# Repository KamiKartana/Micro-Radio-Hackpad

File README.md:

# Hackpad-Mini-Radio-Shaped-Keyboard
A small keyboard to help control settings for a music player easily. While still looking and functioning like an old timey radio. Made as part of the Hackclub Blueprint campaign. The oled display displays the title of the song that is currently playing.

Parts of the radio.

KiCad PCB Final.

KiCad Schematic Final.

Prototype Sketch.

All componets placed together minus the PCB.

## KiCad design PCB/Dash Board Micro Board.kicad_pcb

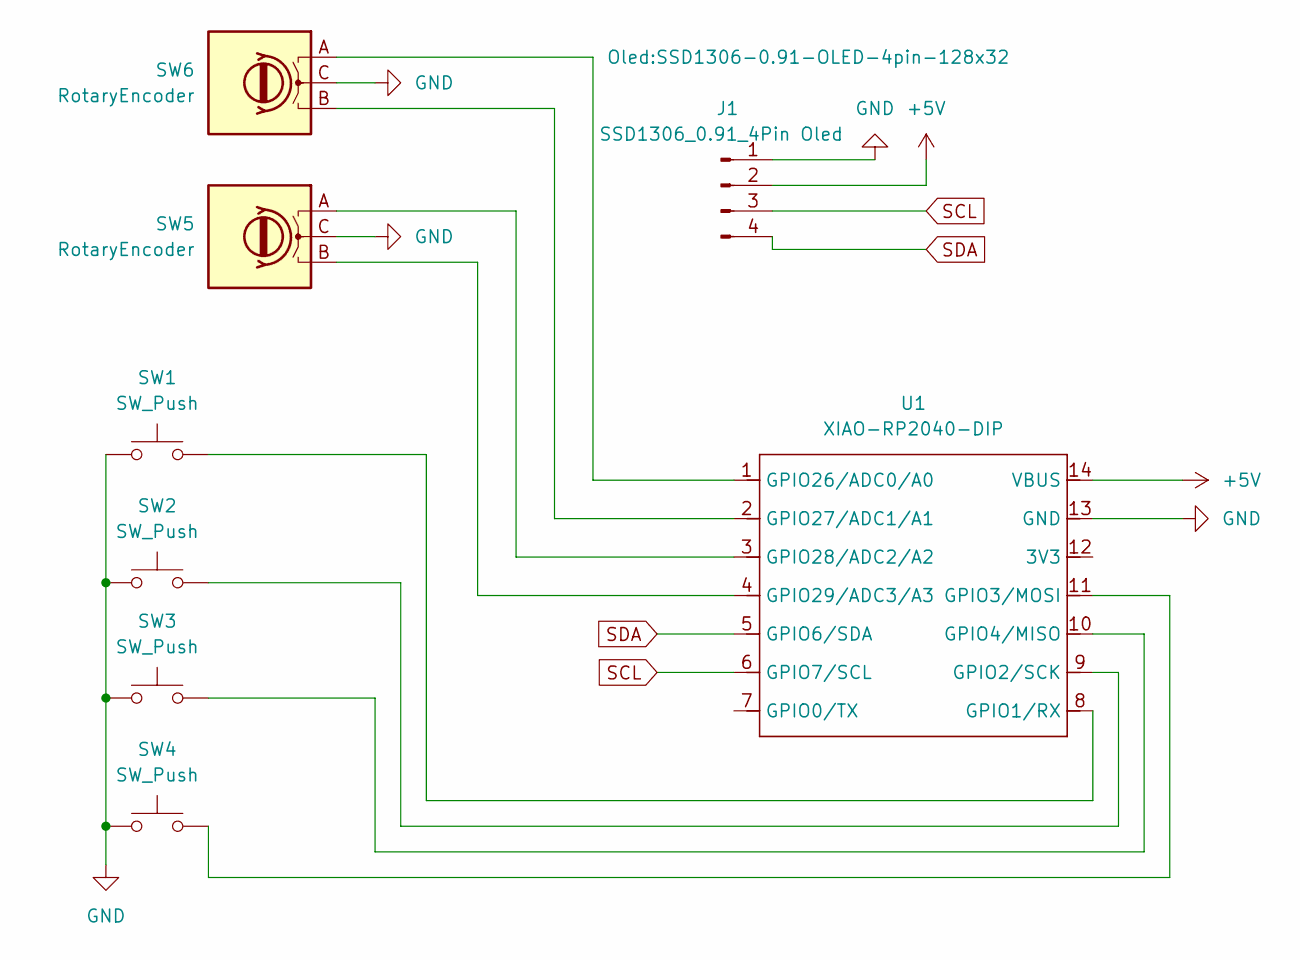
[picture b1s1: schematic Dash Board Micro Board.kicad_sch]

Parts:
J1: SSD1306_0.91_4Pin Oled; SSD1306-0.91-OLED-4pin-128x32
SW1, SW2, SW3, SW4: SW_Push; SW_Cherry_MX_1.00u_PCB
SW5, SW6: RotaryEncoder; RotaryEncoder_Alps_EC11E_Vertical_H20mm
U1: XIAO-RP2040-DIP

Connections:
+5V: J1.2, U1.14 (VBUS)
GND: J1.1, SW1.1, SW2.1, SW3.1, SW4.1, SW5.C, SW6.C, U1.13 (GND)
unnamed: SW1.2, U1.8 (GPIO1/RX)
unnamed: SW2.2, U1.9 (GPIO2/SCK)
unnamed: SW4.2, U1.11 (GPIO3/MOSI)
unnamed: SW3.2, U1.10 (GPIO4/MISO)
unnamed: SW6.A, U1.1 (GPIO26/ADC0/A0)
unnamed: SW6.B, U1.2 (GPIO27/ADC1/A1)
unnamed: SW5.A, U1.3 (GPIO28/ADC2/A2)
unnamed: SW5.B, U1.4 (GPIO29/ADC3/A3)
SCL: J1.3, U1.6 (GPIO7/SCL)
SDA: J1.4, U1.5 (GPIO6/SDA)

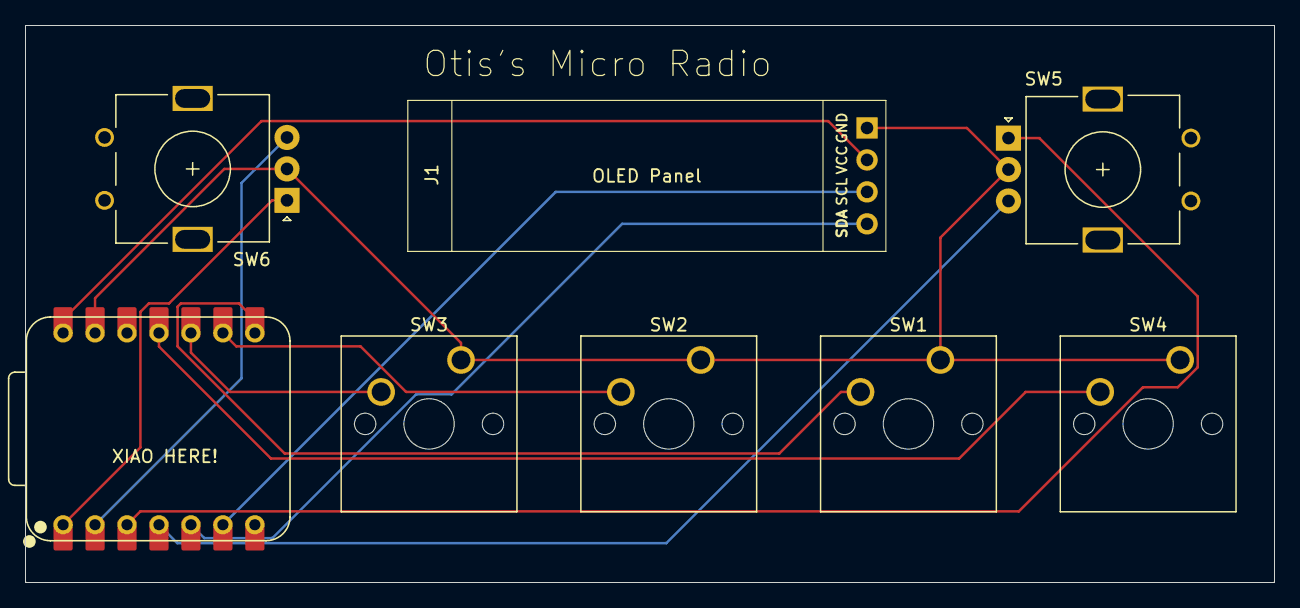
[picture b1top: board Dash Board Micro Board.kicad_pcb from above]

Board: 2 copper layers, 99.3 x 44.3 mm, 8 parts (0 on the bottom side), 12 nets.

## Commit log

2025-12-10 Temp
2025-12-10 Enhance README with images and parts sections
    Added additional images and sections to the README.
2025-12-10 Create temp
